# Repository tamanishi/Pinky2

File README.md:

# Pinky2

A 2 x 5 vertically staggered keys and 3 thumb keys reversible macropad for one hand.  
An idea is inspired from [crkbd](https://github.com/foostan/crkbd), [Lily58](https://github.com/kata0510/Lily58), [Ergo42](https://github.com/Biacco42/Ergo42) and [Helix](https://github.com/MakotoKurauchi/helix).  

## Pcb & Plates

## Bill of Materials

| # | name | qty |
| ---: | :--- | ---: |
| 1 | pcb | 1 |
| 2 | top plate | 1 |
| 3 | bottom plate | 1 |
| 4 | Pro Micro | 1 |
| 5 | Conthrough for Pro Micro | 2 |
| 6 | 2 pins tact switch | 1 |
| 7 | diodes (1N4148 or 1N4148W) | 13 |
| 8 | Kailh PCB Sockets (for MX) | 10 |
| 9 | Kailh PCB Sockets (for Choc) | 3 |
| 10 | Cherry MX compatible keyswitches | 10 |
| 11 | Kailh Choc keyswitches | 3 |
| 12 | Cherry MX compatible keycaps | 10 |
| 13 | Kailh Choc compatible keycaps | 3 |
| 14 | 7mm M2 standoffs (for top and bottom plate) | 3 |
| 15 | 5mm M2 standoffs (for Pro Micro cover plate) | 2 |
| 16 | 4mm M2 screws | 5 |
| 17 | rubber cushions | 4 |

## Firmware

See [Quantum Mechanical Keyboard Firmware](https://qmk.fm) and [its Pinky support page](https://github.com/qmk/qmk_firmware/blob/master/keyboards/pinky/readme.md)

## TODOs

- [ ] add build log

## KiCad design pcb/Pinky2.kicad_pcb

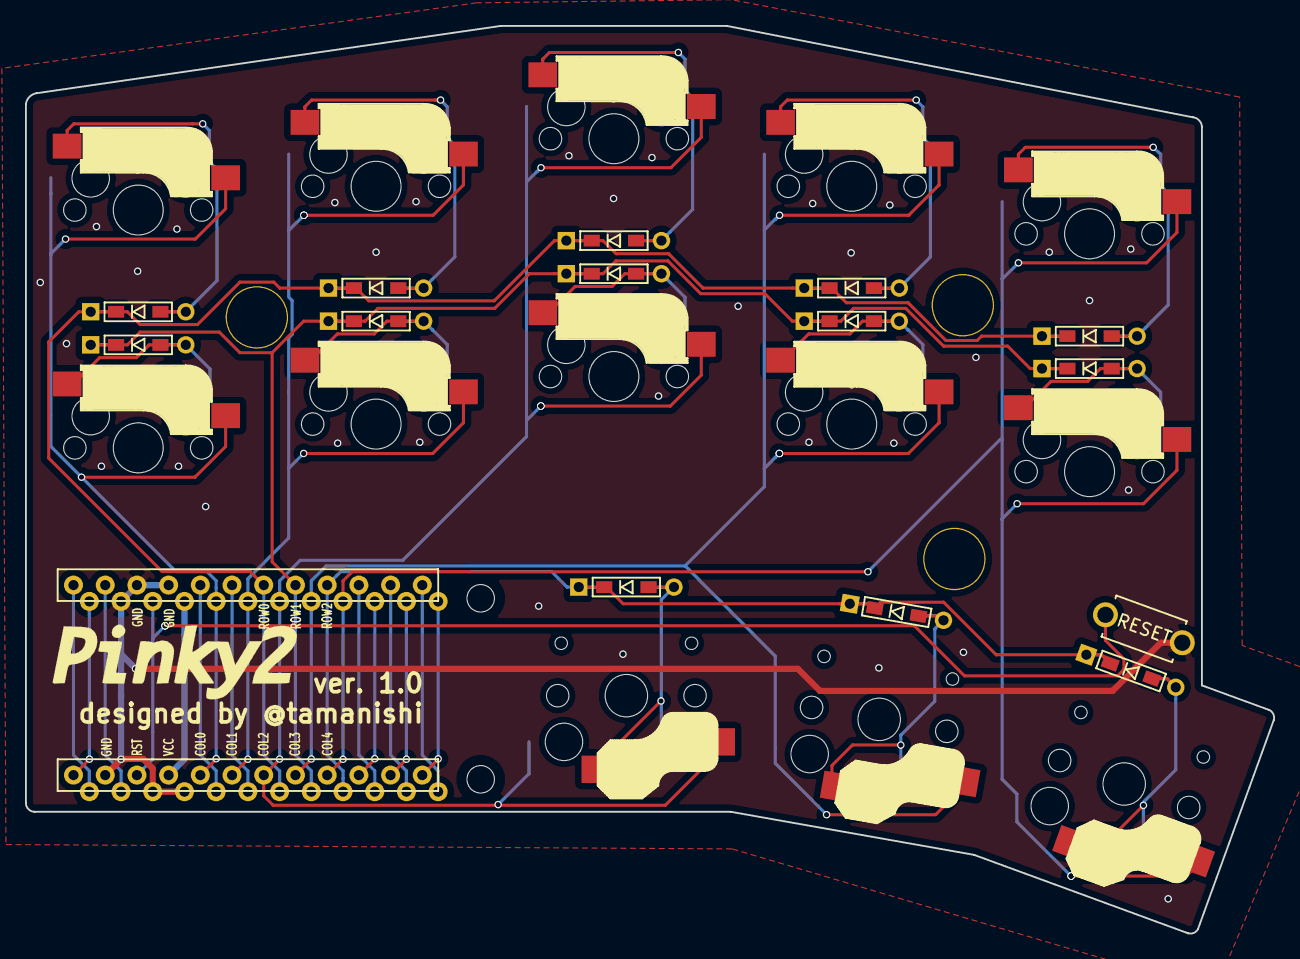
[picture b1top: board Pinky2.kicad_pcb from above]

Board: 2 copper layers, 100.0 x 72.7 mm, 33 parts (0 on the bottom side), 23 nets.

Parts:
D1, D2, D3, D4, D5, D6, D7, D8, D9, D10, D11, D12, D13: D; D3_TH_SMD
HOLE_M2, HOLE_M2#2: VAL**; HOLE_M2
Ref**: Val**; HOLE
Ref**#2, Ref**#3: Val**; HOLE
SW1: RESET_SW; ResetSW
SW2, SW3, SW4, SW5, SW6, SW7, SW9, SW10, SW12, SW13: SW_PUSH; CherryMX_Hotswap
SW8, SW11, SW14: SW_PUSH; Choc_Hotswap
U1: ProMicro; ProMicro_v2

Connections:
GND: SW1.2, U1.3, U1.4, U1.23
unnamed: D1.2, SW2.2
unnamed: D2.2, SW3.2
unnamed: D3.2, SW4.2
unnamed: D4.2, SW5.2
unnamed: D5.2, SW6.2
unnamed: D6.2, SW7.2
unnamed: D7.2, SW8.2
unnamed: D8.2, SW9.2
unnamed: D9.2, SW10.2
unnamed: D10.2, SW11.2
unnamed: D11.2, SW12.2
unnamed: D12.2, SW13.2
unnamed: D13.2, SW14.2
col0: SW2.1, SW3.1, U1.20
col1: SW4.1, SW5.1, U1.19
col2: SW6.1, SW7.1, SW8.1, U1.18
col3: SW9.1, SW10.1, SW11.1, U1.17
col4: SW12.1, SW13.1, SW14.1, U1.16
reset: SW1.1, U1.22
row0: D1.1, D3.1, D5.1, D8.1, D11.1, U1.7
row1: D2.1, D4.1, D6.1, D9.1, D12.1, U1.8
row2: D7.1, D10.1, D13.1, U1.9

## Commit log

2019-10-06 add images
2019-10-08 tweak README.md
2019-10-09 may be finished pcb
2019-10-09 top plate
2019-10-09 design finished
2019-10-09 lighten pbb image
2019-10-22 add product image
2019-10-27 add grabbag ver.
2019-11-27 maintain logo svg file
